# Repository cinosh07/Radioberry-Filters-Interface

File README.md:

# Radioberry beta V3 - Filters Interface companion module.

Radioberry project
https://github.com/pa3gsb/Radioberry-2.x

This project interface LPF, HPF and T/R Switch to the radiobery I/O over i2c.
The logic is arduino nano v3 based microcontroller.

Band pass filters module supported:
https://www.ebay.ca/itm/HF-BPF-band-pass-filter-RTL-SDR-HERMES-ODYSSEY-HiQSDR-Red-Pitaya-transceiver/332074659425?ssPageName=STRK%3AMEBIDX%3AIT&_trksid=p2057872.m2749.l2649

Low pass filters module supported:
https://www.ebay.ca/itm/12v-100W-3-5Mhz-30Mhz-HF-power-amplifier-low-pass-filter-Diy-kit/113761898910?ssPageName=STRK%3AMEBIDX%3AIT&_trksid=p2057872.m2749.l2649

T/R Switch module supported:
https://www.qrpkits.com/ezseries.html#eztrsw

Auto Antenna tuner supported:
https://www.ebay.ca/itm/KIT-DIY-Automatic-Antenna-Tuner-7x7-ATU-100-mini-by-N7DDC/202740242392?ssPageName=STRK%3AMEBIDX%3AIT&_trksid=p2057872.m2749.l2649

Linear PA supported:
https://www.qrp-labs.com/linear.html

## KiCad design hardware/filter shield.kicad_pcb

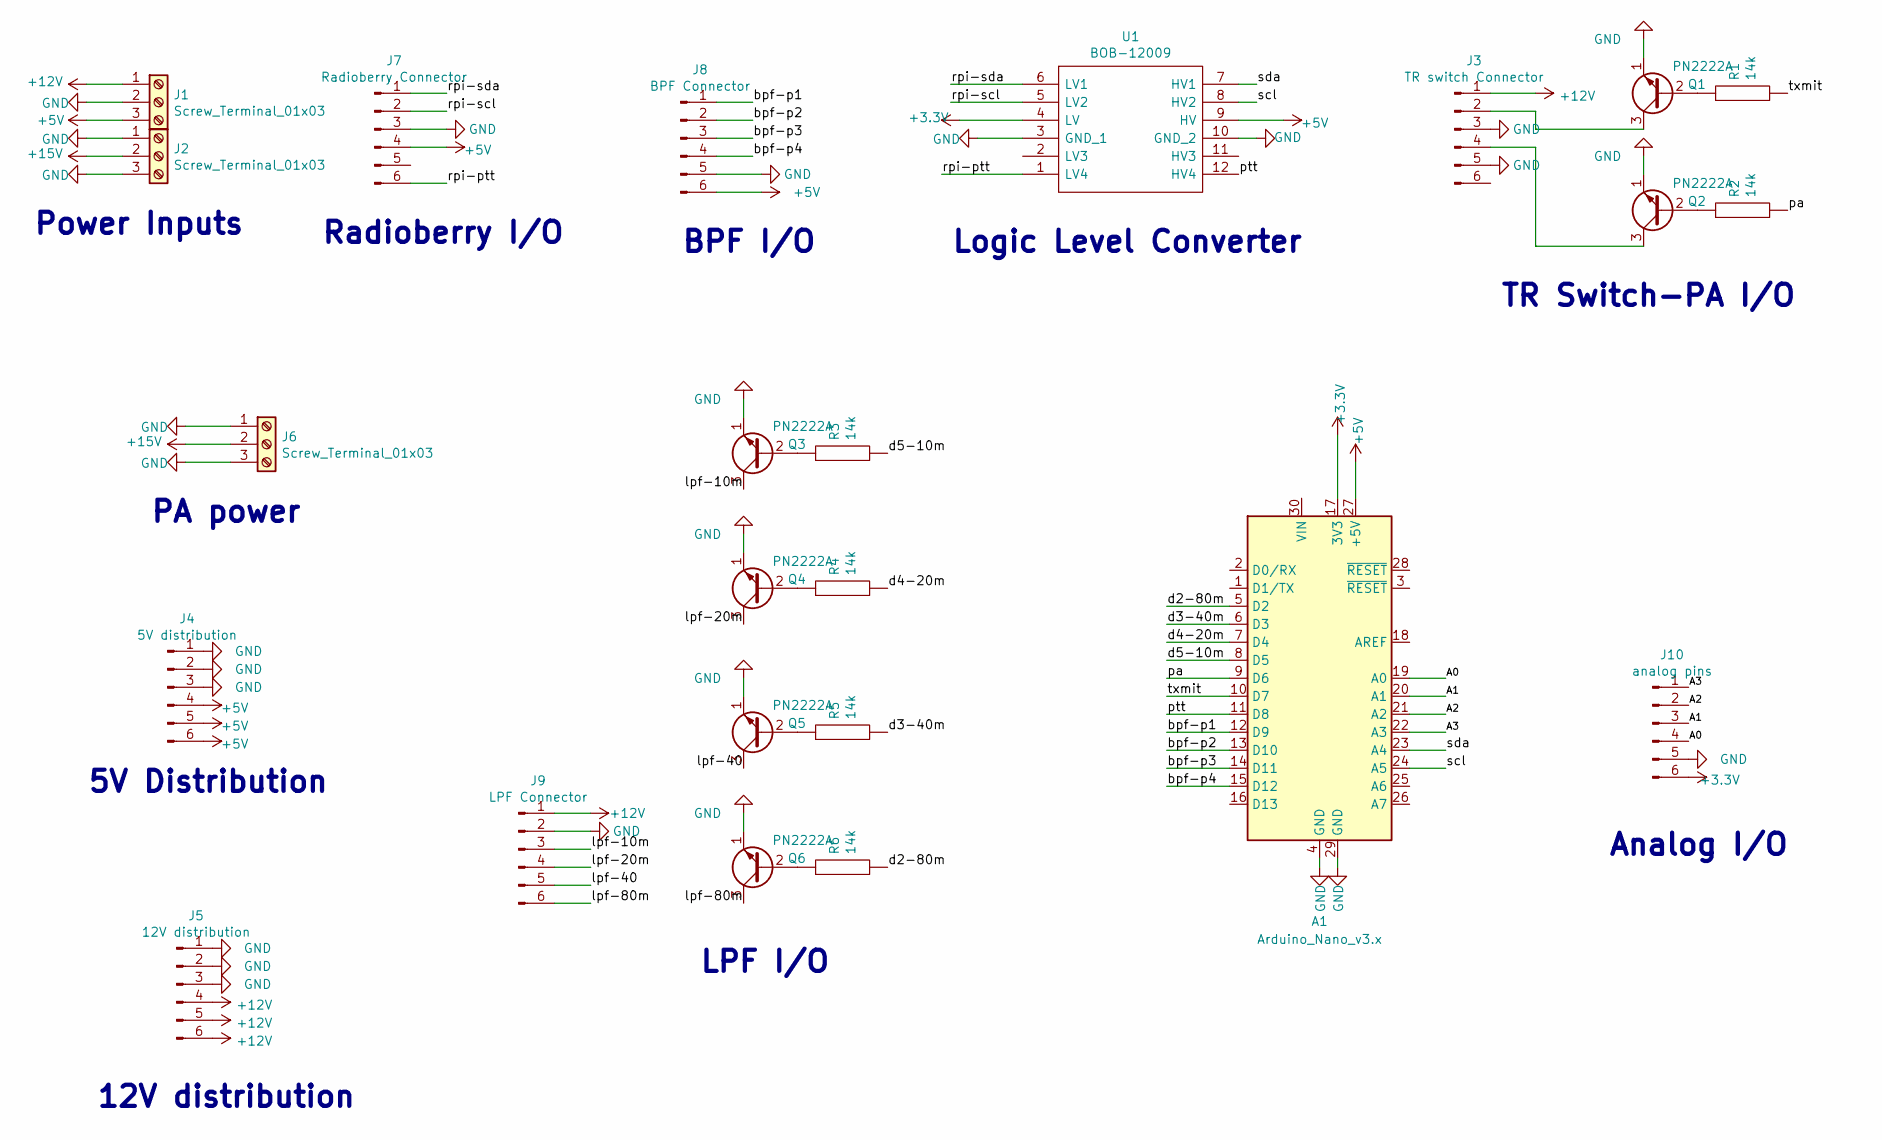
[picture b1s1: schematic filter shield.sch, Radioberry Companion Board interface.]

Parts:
A1: Arduino_Nano_v3.x; Arduino_Nano
J1, J2, J6: Screw_Terminal_01x03; TerminalBlock_Altech_AK300-3_P5.00mm
J3: TR switch Connector; PinHeader_1x06_P2.54mm_Vertical
J4: 5V distribution; PinHeader_1x06_P2.54mm_Vertical
J5: 12V distribution; PinHeader_1x06_P2.54mm_Vertical
J7: Radioberry Connector; PinHeader_1x06_P2.54mm_Vertical
J8: BPF Connector; PinHeader_1x06_P2.54mm_Vertical
J9: LPF Connector; PinHeader_1x06_P2.54mm_Vertical
J10: analog pins; PinHeader_1x06_P2.54mm_Vertical
Q1, Q2, Q3, Q4, Q5, Q6: PN2222A; TO-92_Inline
R1, R2, R3, R4, R5, R6: 14k; R_Axial_DIN0204_L3.6mm_D1.6mm_P7.62mm_Horizontal
U1: BOB-12009; BOB12009; Mouser Part Number 474-BOB-12009

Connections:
+3V3: A1.17 (3V3), J10.6, U1.4 (LV)
+5V: A1.27 (+5V), J1.3, J4.4, J4.5, J4.6, J7.4, J8.6, U1.9 (HV)
+12V: J1.1, J3.1, J5.4, J5.5, J5.6, J9.1
+15V: J2.2, J6.2
/A0: A1.19 (A0), J10.4
/A1: A1.20 (A1), J10.3
/A2: A1.21 (A2), J10.2
/A3: A1.22 (A3), J10.1
/bpf-p1: A1.12 (D9), J8.1
/bpf-p2: A1.13 (D10), J8.2
/bpf-p3: A1.14 (D11), J8.3
/bpf-p4: A1.15 (D12), J8.4
/d2-80m: A1.5 (D2), R6.2
/d3-40m: A1.6 (D3), R5.2
/d4-20m: A1.7 (D4), R4.2
/d5-10m: A1.8 (D5), R3.2
/lpf-10m: J9.3, Q3.3 (C)
/lpf-20m: J9.4, Q4.3 (C)
/lpf-40: J9.5, Q5.3 (C)
/lpf-80m: J9.6, Q6.3 (C)
/pa: A1.9 (D6), R2.2
/ptt: A1.11 (D8), U1.12 (HV4)
/rpi-ptt: J7.6, U1.1 (LV4)
/rpi-scl: J7.2, U1.5 (LV2)
/rpi-sda: J7.1, U1.6 (LV1)
/scl: A1.24 (A5), U1.8 (HV2)
/sda: A1.23 (A4), U1.7 (HV1)
/txmit: A1.10 (D7), R1.2
GND: A1.4 (GND), A1.29 (GND), J1.2, J2.1, J2.3, J3.3, J3.5, J4.1, J4.2, J4.3, J5.1, J5.2, J5.3, J6.1, J6.3, J7.3, J8.5, J9.2, J10.5, Q1.1 (E), Q2.1 (E), Q3.1 (E), Q4.1 (E), Q5.1 (E), Q6.1 (E), U1.3 (GND_1), U1.10 (GND_2)
unnamed: J3.2, Q1.3 (C)
unnamed: J3.4, Q2.3 (C)
unnamed: Q1.2 (B), R1.1
unnamed: Q2.2 (B), R2.1
unnamed: Q3.2 (B), R3.1
unnamed: Q4.2 (B), R4.1
unnamed: Q5.2 (B), R5.1
unnamed: Q6.2 (B), R6.1

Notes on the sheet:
Power Inputs
Radioberry I/O
BPF I/O
LPF I/O
TR Switch-PA I/O
PA power
Logic Level Converter
Analog I/O
5V Distribution
12V distribution

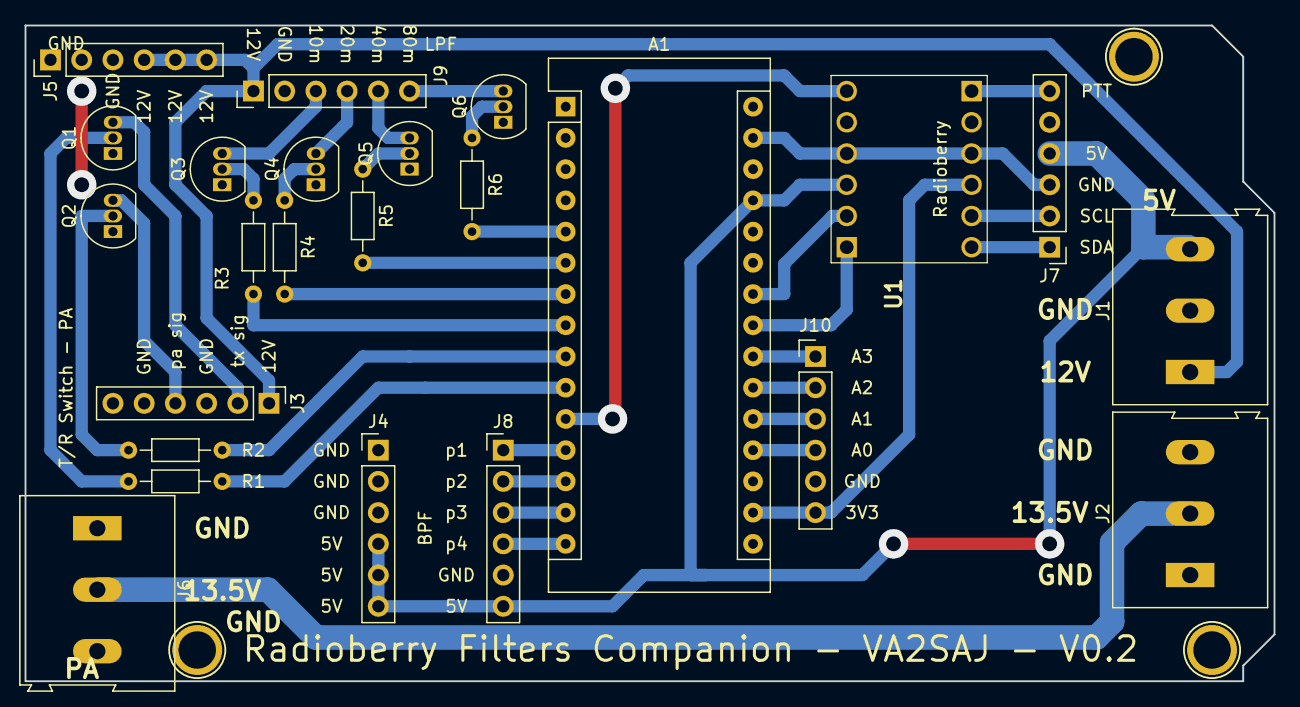
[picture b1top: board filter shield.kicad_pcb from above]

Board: 2 copper layers, 101.6 x 53.3 mm, 27 parts (0 on the bottom side), 37 nets.

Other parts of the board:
P8, P10, P13: CONN_01X01; Arduino_1pin

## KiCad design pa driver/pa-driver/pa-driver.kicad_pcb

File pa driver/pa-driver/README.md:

# Radioberry beta V3 RPI4 - 9db PA Driver Module.

Radioberry project
https://github.com/pa3gsb/Radioberry-2.x

This allow to amplify the RPI4 radioberry version TX output, to suitable level for 10W QRP Labs Linear Power Amplifier.

Mesurement.

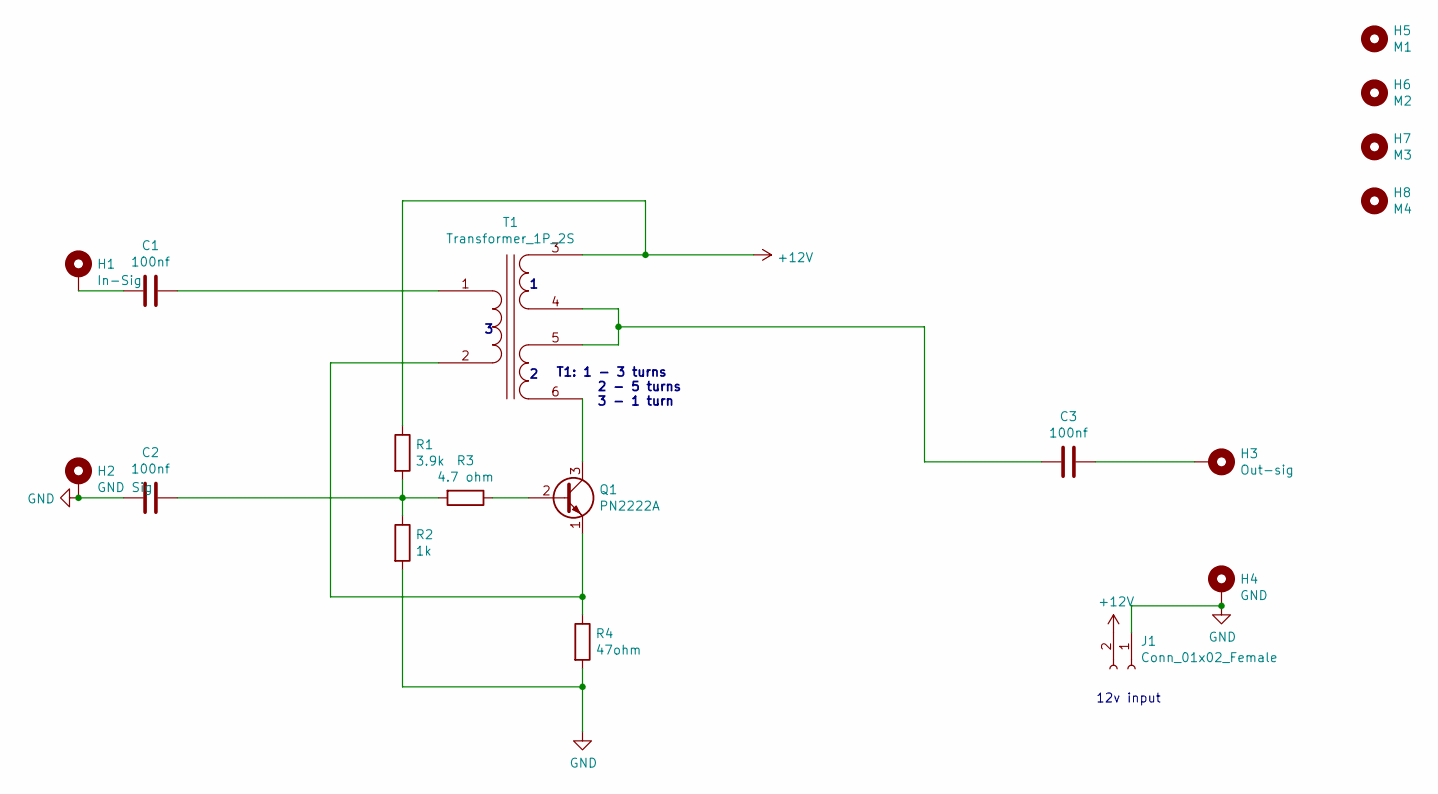
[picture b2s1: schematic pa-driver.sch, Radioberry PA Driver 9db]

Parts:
C1, C2, C3: 100nf; C_Disc_D5.1mm_W3.2mm_P5.00mm
H1: In-Sig; TestPoint_Pad_4.0x4.0mm
H2: GND Sig; TestPoint_Pad_4.0x4.0mm
H3: Out-sig; TestPoint_Pad_4.0x4.0mm
H4: GND; TestPoint_Pad_4.0x4.0mm
H5: M1; MountingHole_3.2mm_M3
H6: M2; MountingHole_3.2mm_M3
H7: M3; MountingHole_3.2mm_M3
H8: M4; MountingHole_3.2mm_M3
J1: Conn_01x02_Female; PinHeader_1x02_P2.54mm_Vertical
Q1: PN2222A; TO-92_Inline
R1: 3.9k; R_Axial_DIN0204_L3.6mm_D1.6mm_P5.08mm_Vertical
R2: 1k; R_Axial_DIN0204_L3.6mm_D1.6mm_P5.08mm_Vertical
R3: 4.7 ohm; R_Axial_DIN0204_L3.6mm_D1.6mm_P5.08mm_Vertical
R4: 47ohm; R_Axial_DIN0204_L3.6mm_D1.6mm_P5.08mm_Vertical
T1: Transformer_1P_2S; Transformer2 1p 2s Binocular

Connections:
+12V: J1.2, R1.1, T1.3 (SA)
GND: C2.2, H2.1, H4.1, J1.1, R2.2, R4.2
unnamed: C1.1, T1.1 (AA)
unnamed: C1.2, H1.1
unnamed: C2.1, R1.2, R2.1, R3.2
unnamed: C3.1, H3.1
unnamed: C3.2, T1.4 (SB), T1.5 (SC)
unnamed: Q1.1 (E), R4.1, T1.2 (AB)
unnamed: Q1.2 (B), R3.1
unnamed: Q1.3 (C), T1.6 (SD)

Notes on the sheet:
T1: 1 - 3 turns 2 - 5 turns 3 - 1 turn
12v input

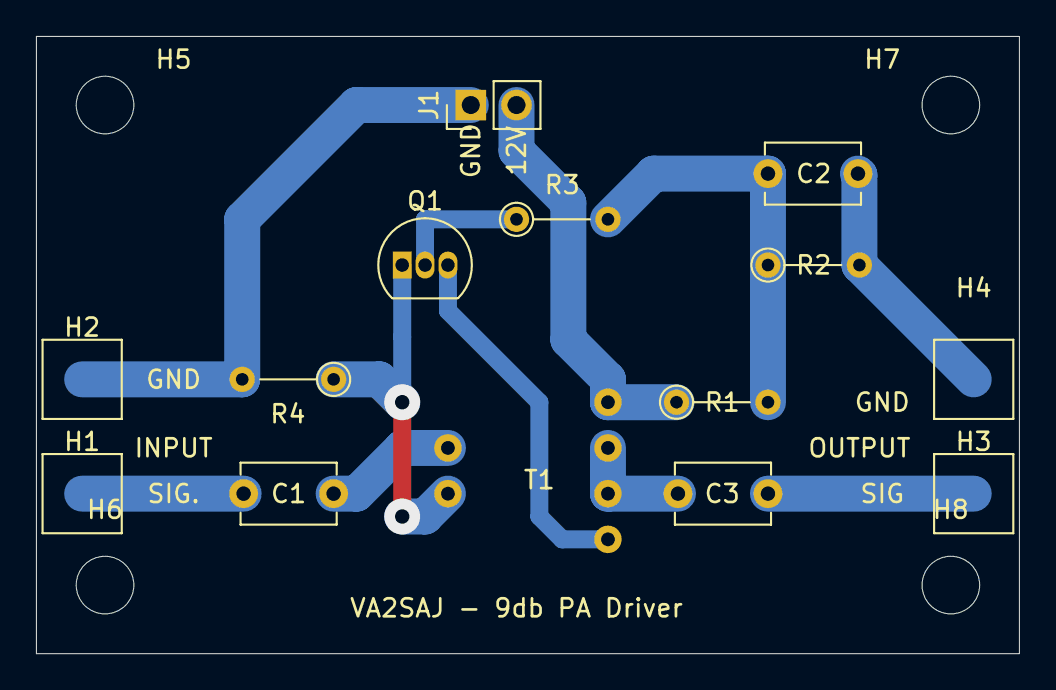
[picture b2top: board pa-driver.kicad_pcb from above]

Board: 2 copper layers, 54.6 x 34.3 mm, 18 parts (0 on the bottom side), 10 nets.

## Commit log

2020-02-19 Hardware Kitcad files
2020-02-19 Arduino firmware
2020-02-20 tr switch circuit added
2020-02-21 First version completed and ready to etch.
2020-02-21 Added images for documentions
2020-02-25 Small corrections
2020-02-27 Revised circuit to meet lpf protocol. Added futur expansion i/o over analog pins
2020-02-27 Small changes
2020-02-27 Modif to silk
2020-02-29 Change screw terminal to 5mm footprint
2020-03-01 Modif to pin assignment
2020-03-02 Modif to error in the silk of pcb
2020-03-04 Added 9db pa driver schematics
2020-03-09 9db PA Driver modification
2020-04-21 Modif to PA driver
2020-04-21 Added png capture
2020-05-01 Addded CWX and MOX Status
